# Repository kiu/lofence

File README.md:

# LoFence
LoFence is a [LoRaWAN](https://en.wikipedia.org/wiki/LoRa#LoRaWAN) capable IoT electric fence monitoring system running on the [The Things Network](https://www.thethingsnetwork.org/).

# Backstory
A friend of mine is herding cattle and sheep on a small scale as a hobby. His setup is quite clever as his property has a creek running through, which enables him to let the animals live quite autonomously with minimal supervision. Unfortunately, he got called by the police a few times due to his sheep pulling a prison break. In theory a low maintenance system, but in reality things do happen. The car battery powering the electric fence energizer runs out of juice, a falling tree branch tears the fence down, or a tractor plows down a pole of the fence.

# Obvious solution
We need a monitoring system!

## Measuring
There are lots of ways to measure an electric fence. Try to hack the energizers built-in fault detection, measure current or do some fancy wave analysis of reflections on the line.

Too complicated for the initial build, lets keep it simple by measuring voltage. Well, not a little voltage, but all the way up to 12 kV. Difficult, but a voltage divider with an op-amp will do fine. With this setup, we can measure any disconnects on the line between the energizer and the LoFence measuring point, even short circuits after the measuring point. Your mileage may vary though. This setup is heavily dependent on weather conditions, e.g. having dry soil will provide a different readout than after heavy rain.

## Connectivity
The more difficult challenge in a rural/agricultural area is connectivity. Cell coverage is quite spotty and of course it requires a monthly payment of some kind. Further, its such a 90s solution to use a GSM module.

A few years ago LoRa appeared on the stage operating in the freely available [ISM bands](https://en.wikipedia.org/wiki/ISM_band) offering low speed, long range communication. Perfect for...sigh...IoT devices like the LoFence. While LoRa is great for point-to-point communication, LoRaWAN got established and offers a full suite of protocols enabling a standardized way to build communication networks based on LoRa. While there are commercial network operators like [Sigfox](https://www.sigfox.com) where you have to pay for their services, there is a global initiative called [The Things Network](https://www.thethingsnetwork.org/) to run an open LoRaWAN network that any device can join and use for free. Bingo.

Checking their [coverage map](https://www.thethingsnetwork.org/map) of course showed that the area of interest has no gateways in reach, but setting up a simple [gateway](https://raw.githubusercontent.com/kiu/lofence/master/pics/lofence_ttig.jpg) - in our case a [TTIG](https://www.thethingsnetwork.org/forum/t/ttig-the-things-indoor-gateway/22049) for ~80 Euro - easily solved the coverage problem. According to their [Fair Access Policy](https://www.thethingsnetwork.org/forum/t/limitations-data-rate-packet-size-30-seconds-uplink-and-10-messages-downlink-per-day-fair-access-policy/1300) our use-case of sending a few bytes of measurement data every few hours is perfectly fitted for their service. Lets roll.

There are quite a few options to integrate LoRaWAN into your device. From the super cheap [RFM95W chipset](https://www.hoperf.com/modules/lora/RFM95.html) where your firmware has to do most of the action (e.g. used by the [Adafruit Feather](https://www.adafruit.com/product/3078)), up to the "expensive" turnkey solution like the [RN2483](https://www.microchip.com/wwwproducts/en/RN2483) which I chose. It does all the magic and will actively prevent you from breaking ISM band regulations regarding radio utilization. Nice.
 
## Build
The build is quite unspectacular. Spinning up a board with some AVR, put an antenna and the RN2483 on it, a big resistor divider with an op-amp and some resistors, debug LEDs and pin headers, an 18650 battery and a waterproof case. Et voila.

## Data Extraction
Having a node reporting its measurements to The Things Network is nice, but actually I want to do something with the data. Like sending an alert.

Extracting the data from TTN is easy, but I did it wrong anyways. First thing I stumbled upon was the [HTTP Integration](https://www.thethingsnetwork.org/docs/applications/http/). Everytime an uplink message is received from a node, the HTTP integration will trigger a POST message to a webserver of your choice. Great. So I wrote a Java service on my end to parse these messages and store them in a database for [grafana](https://grafana.com/) to [consume](https://raw.githubusercontent.com/kiu/lofence/master/pics/lofence_grafana_overview.png) later on. My implementation parses the uplink message, extracts the payload, stores the RSSI, SNR, number of gateways, etc. It can be found here: [ttn-http](https://github.com/kiu/ttn-http).

Later, I found out that there is a way nicer [MQTT Integration](https://www.thethingsnetwork.org/docs/applications/mqtt/), which also includes a ready to use Java implementation. A couple of hours could have been saved here.

The other thing I didn't figure out immediately is the [Payload Formats](https://raw.githubusercontent.com/kiu/lofence/master/pics/lofence_ttn_decoder.png) option in the TTN console. It lets you write simple javascript running inside The Things Network to decode your payload data and assign them to key-value pairs. When receiving a message through the HTTP Integration (or MQTT), that message will include the key-value pairs as json for easy consumption. Quite clever and easy to parse.

# Nitty-Gritty Details
Checkout the [pics](https://github.com/kiu/lofence/tree/master/pics) and [hardware](https://github.com/kiu/lofence/tree/master/rev_b) section including BOM, Schematic, PCB layout, firmware, etc.

# TTN
If you are inspired by this hack to build a LoRaWAN project on your own and join the The Things Network effort, register on their site and join their maker community on [slack](https://www.thethingsnetwork.org/community/toowoomba/post/join-us-on-slack).

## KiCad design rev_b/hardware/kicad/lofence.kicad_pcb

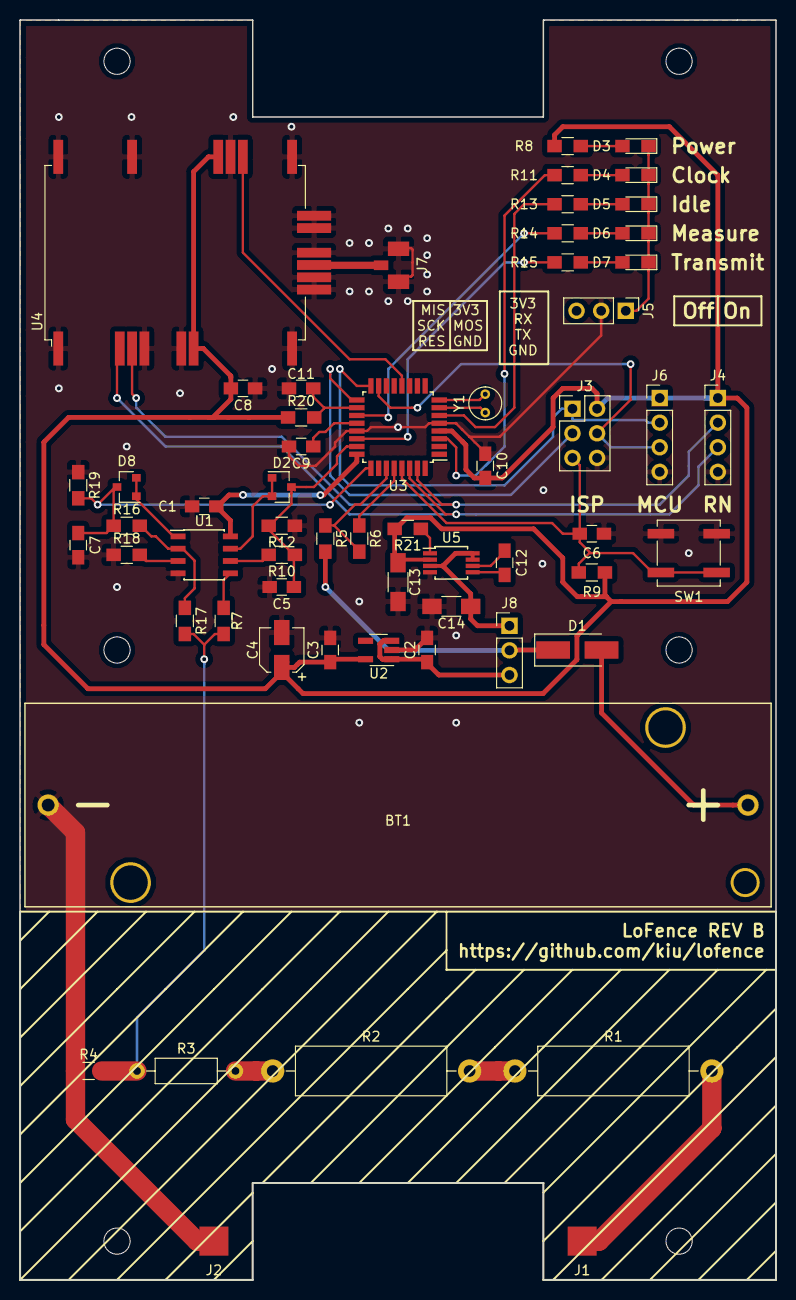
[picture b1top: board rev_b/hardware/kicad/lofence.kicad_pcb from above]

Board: 2 copper layers, 78.0 x 130.0 mm, 65 parts (0 on the bottom side), 46 nets.

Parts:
BT1: Battery_Cell; 18650HolderTHT
C1, C5, C6, C7, C8, C9, C10, C11: 100nF; C_0805_HandSoldering
C2, C3: 1.0uF; C_0805_HandSoldering
C4: 10uF; CP_Elec_4x5.7
C12: 1uF; C_0805_HandSoldering
C13, C14: 10uF; C_1206_HandSoldering
D1: D_Schottky; D_SMA_Handsoldering
D2, D8: BAV70LT; SOT-23
D3, D4, D5, D6, D7: LED; LED_0805_HandSoldering
J1: Fence+; Measurement_Point_Square-SMD-Pad_Big
J2: Fence-; Measurement_Point_Square-SMD-Pad_Big
J3: ISP; Pin_Header_Straight_2x03_Pitch2.54mm
J4: DEBUG RN; Pin_Header_Straight_1x04_Pitch2.54mm
J5: DEBUG LED; Pin_Header_Straight_1x03_Pitch2.54mm
J6: DEBUG MCU; Pin_Header_Straight_1x04_Pitch2.54mm
J7: 868; U.FL
J8: PWR; Pin_Header_Straight_1x03_Pitch2.54mm
MH1, MH2, MH3, MH4, MH5, MH6: MountingHole; MountingHole_2.7mm_M2.5
R1, R2: 10M 6KV; R_Axial_DIN0516_L15.5mm_D5.0mm_P20.32mm_Horizontal
R3: 1M 700V; R_Axial_DIN0207_L6.3mm_D2.5mm_P10.16mm_Horizontal
R4: 3k9; R_0805_HandSoldering
R5, R6: 232R; R_0805_HandSoldering
R7, R10, R16, R17, R18, R21: 100k; R_0805_HandSoldering
R8, R11, R13, R14, R15: R; R_0805_HandSoldering
R9: 4k7; R_0805_HandSoldering
R12, R19: 1M; R_0805_HandSoldering
R20: 47R; R_0805_HandSoldering
SW1: RESET; SW_SPST_B3SL-1002P
U1: Opamp_Dual_Generic; SOIC-8_3.9x4.9mm_Pitch1.27mm
U2: MIC5504-3.3YM5; SOT-23-5_HandSoldering
U3: ATmega328PB-AU; TQFP-32_7x7mm_Pitch0.8mm
U4: RN2483; RN2483_serial
U5: MCP125x; MSOP-8_3x3mm_Pitch0.65mm
Y1: 32768 Hz; Crystal_Round_d3.0mm_Vertical

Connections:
+3V3: C3.1, C4.1, C8.2, C10.2, C13.1, J3.2, J4.1, J6.1, R8.2, R9.1, R20.1, R21.2, U2.5, U3.4, U4.12, U4.34, U5.2
ADC+: C5.1, D2.3, R10.1, R12.2, U3.23
ADC-: C7.1, D8.3, R16.1, R19.2, U3.25
ADC_POWER: C1.1, U1.8, U3.24
AVCC: C11.2, R20.2, U3.18
BAT_ADC: R5.1, R6.2, U3.27
BAT_GND: R6.1, U3.28
BAT_VCC: D1.1, J8.2, R5.2
GND: BT1.2, C1.2, C2.2, C3.2, C4.2, C5.2, C6.2, C7.2, C8.1, C9.2, C10.1, C11.1, C13.2, C14.2, J2.1, J3.6, J4.4, J5.2, J6.4, J7.2, R4.1, R12.1, R18.1, R19.1, SW1.2, U1.4, U2.2, U3.5, U3.21, U4.1, U4.8, U4.11, U4.20, U4.21, U4.22, U4.24, U4.26, U4.27, U4.28, U4.33, U4.41, U4.47, U5.4
LED_CLK: R11.2, U3.3
LED_IDLE: R13.2, U3.6
LED_MSR: R14.2, U3.19
LED_TX: R15.2, U3.22
MCU_MISO: J3.1, J6.2, U3.16
MCU_MOSI: J3.4, J6.3, U3.15
MCU_RESET: C6.1, J3.5, R9.2, SW1.1, U3.29
MCU_SCK: J3.3, U3.17
unnamed: BT1.1, D1.2
unnamed: C9.1, U3.20
unnamed: C12.1, U5.6
unnamed: C12.2, U5.5
unnamed: D2.1, D2.2, U1.7
unnamed: D3.1, D4.1, D5.1, D6.1, D7.1, J5.1
unnamed: D3.2, R8.1
unnamed: D4.2, R11.1
unnamed: D5.2, R13.1
unnamed: D6.2, R14.1
unnamed: D7.2, R15.1
unnamed: D8.1, D8.2, U1.1
unnamed: J1.1, R1.2
unnamed: J7.1, U4.23
unnamed: R1.1, R2.2
unnamed: R2.1, R3.2
unnamed: R7.1, U1.5
unnamed: R10.2, U1.6
unnamed: R16.2, R17.1, U1.2
unnamed: R18.2, U1.3
unnamed: R21.1, U5.1
unnamed: U3.7, Y1.1
unnamed: U3.8, Y1.2
PROBE: R3.1, R4.2, R7.2, R17.2
RN_RESET: U3.12, U4.32
RN_RX: J4.2, U3.31, U4.7
RN_TX: J4.3, U3.30, U4.6
VCC_BBC: C14.1, J8.1, U5.3, U5.7, U5.8
VCC_LDO: C2.1, J8.3, U2.1, U2.3

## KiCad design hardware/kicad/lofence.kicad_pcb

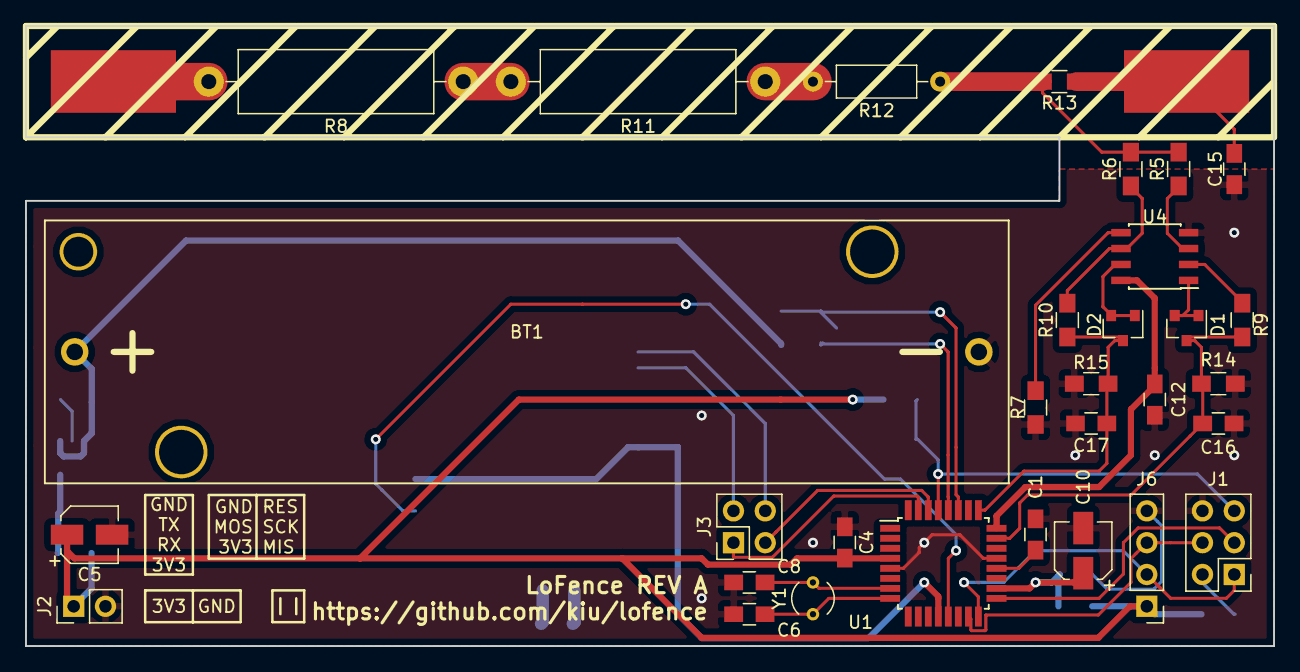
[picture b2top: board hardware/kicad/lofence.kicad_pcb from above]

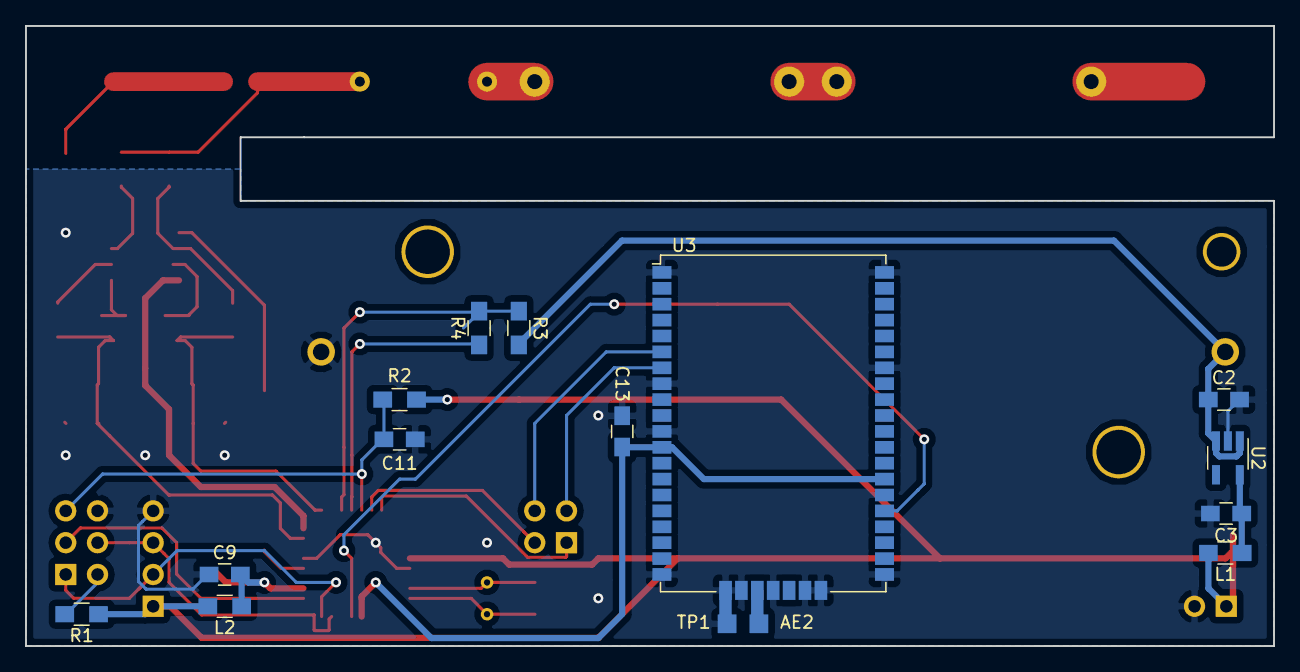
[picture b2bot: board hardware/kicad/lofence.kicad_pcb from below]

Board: 2 copper layers, 99.7 x 49.5 mm, 48 parts (15 on the bottom side), 36 nets.

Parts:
AE2: Antenna; Measurement_Point_Square-SMD-Pad_Small
BT1: Battery_Cell; 18650HolderTHT
C1, C4, C9, C11, C12, C13, C16, C17: 100nF; C_0805_HandSoldering
C2, C3: 1.0uF; C_0805_HandSoldering
C5, C10: 10uF; CP_Elec_4x5.7
C6, C8: 0pF; C_0805_HandSoldering
C15: 0nF; C_0805_HandSoldering
D1, D2: BAV70LT; SOT-23
J1: ISP; Pin_Header_Straight_2x03_Pitch2.54mm
J2: POWER; Pin_Header_Straight_1x02_Pitch2.54mm
J3: DEBUG RN2483; Pin_Header_Straight_2x02_Pitch2.54mm
J5: Fence+; SolderWirePad_single_SMD_5x10mm
J6: DEBUG RXTX; Pin_Header_Straight_1x04_Pitch2.54mm
J7: Fence-; SolderWirePad_single_SMD_5x10mm
L1: 10uH; R_0805_HandSoldering
L2: Ferrite_Bead; R_0805_HandSoldering
R1: 0R; R_0805_HandSoldering
R2: 4k7; R_0805_HandSoldering
R3, R4: 232R; R_0805_HandSoldering
R5, R6, R7, R9, R10: 100k; R_0805_HandSoldering
R8, R11: 10M 6KV; R_Axial_DIN0516_L15.5mm_D5.0mm_P20.32mm_Horizontal
R12: 1M 700V; R_Axial_DIN0207_L6.3mm_D2.5mm_P10.16mm_Horizontal
R13: 3k9; R_0805_HandSoldering
R14, R15: 1M; R_0805_HandSoldering
TP1: TestPoint; Measurement_Point_Square-SMD-Pad_Small
U1: ATmega328PB-AU; TQFP-32_7x7mm_Pitch0.8mm
U2: MIC5504-3.3YM5; SOT-23-5_HandSoldering
U3: RN2483
U4: Opamp_Dual_Generic; SOIC-8_3.9x4.9mm_Pitch1.27mm
Y1: 32768 Hz; Crystal_AT310_d3.0mm_l10.0mm_Vertical

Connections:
+3.3VADC: C9.2, C10.1, L2.1, U1.18
+3V3: C4.2, C5.1, J2.1, J6.1, L1.2, L2.2, R1.1, R2.1, U1.4
ADC+: C16.1, D1.3, R9.1, R14.2, U1.23
ADC-: C17.1, D2.3, R10.1, R15.2, U1.25
ADC_POWER: C12.2, U1.24, U4.8
BAT_ADC: R3.1, R4.2, U1.27
BAT_GND: R4.1, U1.28
BAT_VCC: BT1.1, C2.1, R3.2, U2.1, U2.3
GND: BT1.2, C1.2, C2.2, C3.2, C4.1, C5.2, C6.1, C8.1, C9.1, C10.2, C11.2, C12.1, C13.1, C15.2, C16.2, C17.2, J1.6, J2.2, J6.4, R7.1, R14.1, R15.1, TP1.1, U1.5, U1.21, U2.2, U3.1, U3.8, U3.11, U3.20, U3.21, U3.22, U3.24, U3.26, U3.27, U3.28, U3.33, U3.41, U3.47, U4.4
MCU_DBG_RX: J1.1, J6.2, U1.16
MCU_DBG_TX: J1.4, J6.3, U1.15
MCU_RESET: C11.1, J1.5, R2.2, U1.29
MCU_RX: J3.3, U1.30
MCU_SCK: J1.3, U1.17
MCU_TX: J3.1, U1.31
unnamed: AE2.1, U3.23
unnamed: C1.1, U1.20
unnamed: C3.1, L1.1, U2.5
unnamed: C6.2, U1.8, Y1.1
unnamed: C8.2, U1.7, Y1.2
unnamed: C15.1, J7.1, R13.1
unnamed: D1.1, D1.2, U4.1
unnamed: D2.1, D2.2, U4.7
unnamed: J1.2, R1.2
unnamed: J5.1, R8.2
unnamed: R5.1, U4.3
unnamed: R7.2, U4.5
unnamed: R9.2, U4.2
unnamed: R6.1, R10.2, U4.6
unnamed: R11.1, R12.2
unnamed: R8.1, R11.2
PROBE: R5.2, R6.2, R12.1, R13.2
RN_POWER: C13.2, U1.12, U3.12, U3.34
RN_RESET: U1.13, U3.32
RN_RX: J3.2, U3.7
RN_TX: J3.4, U3.6

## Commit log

2019-03-25 init REV A
2019-08-15 REV B is ready for real world usage
2019-08-16 clean up files
2019-08-16 Better late than never
2019-08-16 Added readme
2019-08-16 Fixed readme
2020-02-09 Corrected value of R4 in BOM
2020-07-23 .lib shouldn't be ignored, the cache file is required.
2020-09-17 Fixed BOM for R5 + R6 (0805 instead of 1206)
2020-09-17 Fixed silkscreen for ISP connector
2020-09-17 Increased interval to respect TTN fair use policy and enabled ADR as required for SF12BW125
2021-10-18 Update tts_v3_payload_formatter.js
    Use @kiu's example. Just replaced German with English.
2021-10-18 Use OTAA join
2022-03-28 Move radio functions to dedicated c and h files.
